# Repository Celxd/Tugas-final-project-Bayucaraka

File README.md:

# Data Kelompok

| Nama | NRP | Prodi | Sub-divisi |
| --- | --- | --- | --- |
| Alif Gibran Muhammad Ervin | 5026251070 | Sistem Informasi | Programming |
| Kadek Rahayu Pradnyani | 2040251079 | Teknik Elektro Otomasi | Electrical |
| Ahmad Syahreza Nouval Siregar | 5002251169 | Matematika | Mekanik |

# Struktur Project
```
.
├── Electrical/
│   ├── Old/            (Demo Elektrikal)
│   ├── Revised/        (Revisi Elektrikal)
├── Mechanical/
│   ├── ...
├── Programming/
│   ├── revised_ros_ws/ (Revisi Programming)
│   └── OLD_final.py    (Demo Programming)
├── .gitignore
└── README.md
```

# Electrical
Beberapa peningkatan atau perbaikan yang dilakukan:  
- Ground plane ditempatkan di layer atas, sehingga distribusi ground lebih rapi dan stabil.
- Jalur sinyal dan jalur lainnya berada di layer bawah, untuk mempermudah routing dan meningkatkan connectivity antar komponen.
- Desain ini dibuat dengan mempertimbangkan kemudahan proses produksi di Toko Panut, sehingga layout lebih clean dan tidak terlalu kompleks untuk menyolder saat sudah dicetak.
- Clearance antar jalur diperlebar, sehingga proses penyolderan menjadi lebih mudah dan mengurangi risiko short circuit.

Secara desain dan layout, PCB sudah siap untuk tahap produksi dan assembly.

Namun, untuk saat ini pengujian penggerakan motor belum dapat dilakukan karena tidak dapat meminjam motor untuk dicoba.

# Programming
Logika awal programming:
- Cam detect tag0(payload)
- Send posisi tag0 ke mcu sampai tag0 dekat 0,0
- Send command "PAYLOAD" ke mcu agar mcu menggerakkan motor untuk mengambil payload
- Mcu mengirimkan command track drop lalu cam mendeteksi tag1
- Cam mengirimkan posisi tag1 ke mcu sampai tag1 dekat 0,0
- Mcu mengirimkan command "DROP" ke mcu agar mcu menggerakkan motor untuk menjatuhkan payload

Revisi (``Programming\revised_ros_ws``):
- Menggantikan koneksi langsung dengan serial menjadi koneksi melalui topic

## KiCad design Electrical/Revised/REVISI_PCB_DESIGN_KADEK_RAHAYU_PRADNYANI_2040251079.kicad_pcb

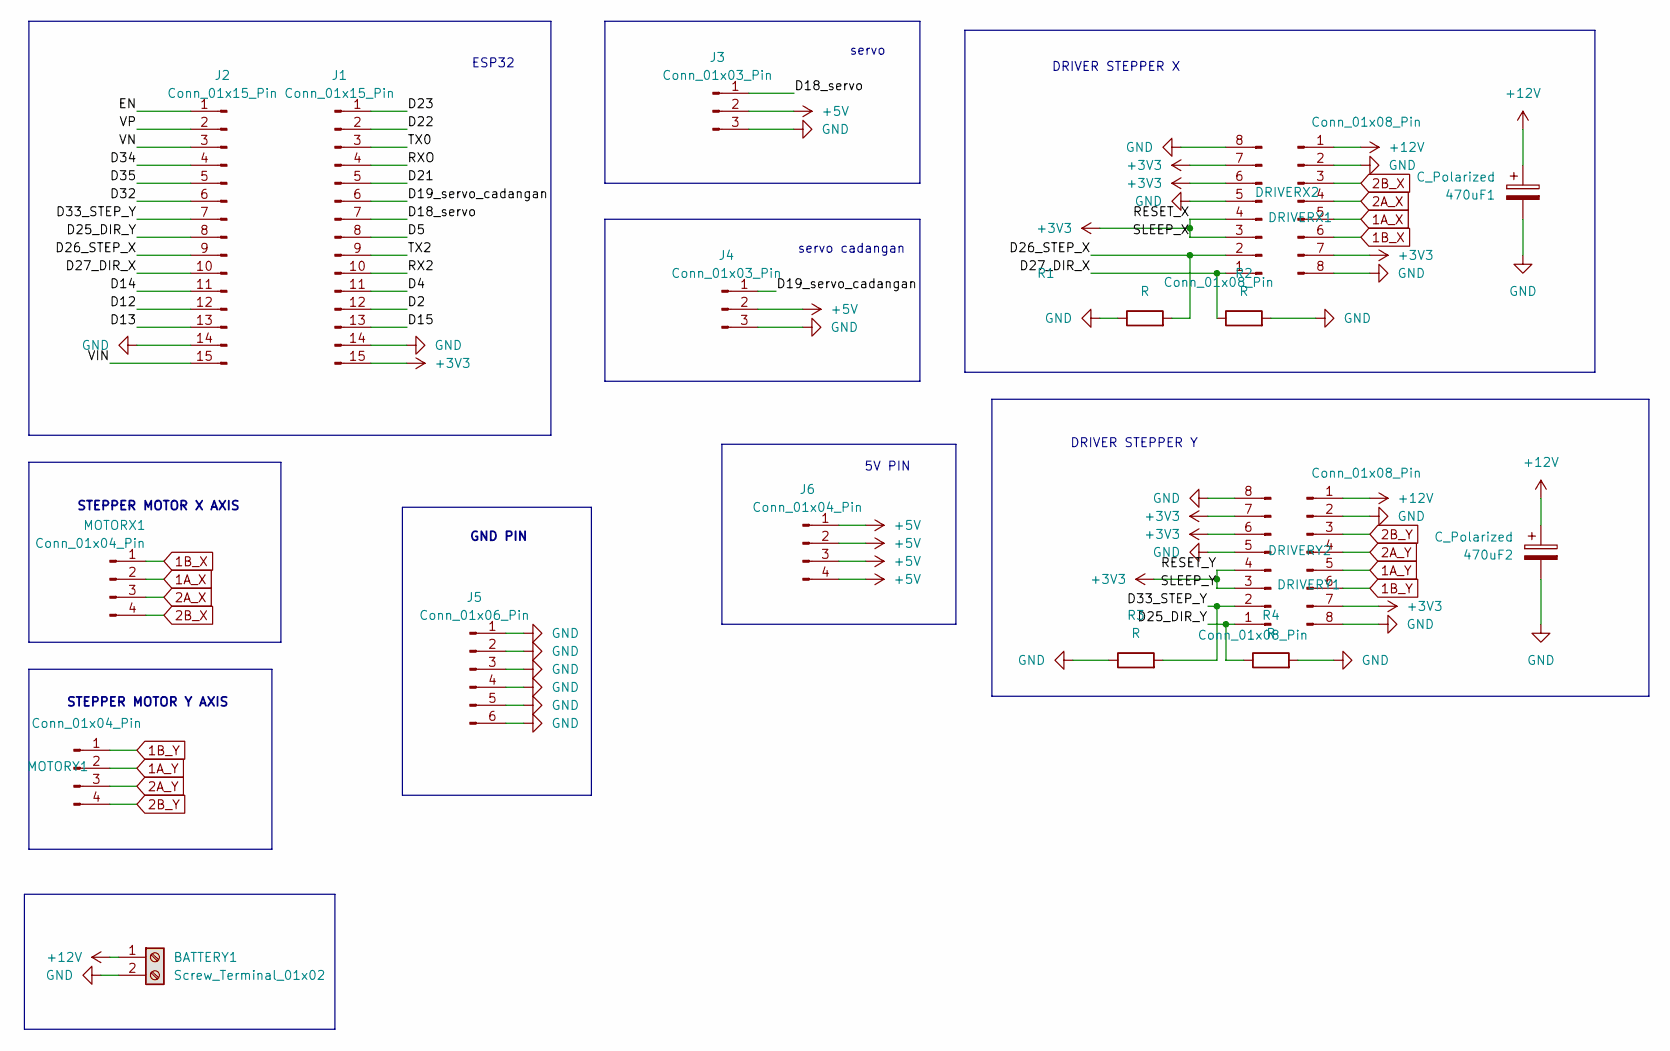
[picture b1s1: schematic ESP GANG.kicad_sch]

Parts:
470uF1, 470uF2: C_Polarized; CP_Radial_D8.0mm_P3.50mm
BATTERY1: Screw_Terminal_01x02; TerminalBlock_Phoenix_PT-1,5-2-3.5-H_1x02_P3.50mm_Horizontal
DRIVERX1, DRIVERX2: Conn_01x08_Pin; PinSocket_1x08_P2.54mm_Vertical
DRIVERY1, DRIVERY2: Conn_01x08_Pin; PinSocket_1x08_P2.54mm_Vertical
J1, J2: Conn_01x15_Pin; PinHeader_1x15_P2.54mm_Vertical
J3, J4: Conn_01x03_Pin; PinHeader_1x03_P2.54mm_Vertical
J5: Conn_01x06_Pin; PinSocket_1x06_P2.54mm_Vertical
J6: Conn_01x04_Pin; PinSocket_1x04_P2.54mm_Vertical
MOTORX1: Conn_01x04_Pin; PinSocket_1x04_P2.54mm_Vertical
MOTORY1: Conn_01x04_Pin; PinSocket_1x04_P2.54mm_Vertical
R1, R2, R3, R4: R; R_Axial_DIN0207_L6.3mm_D2.5mm_P7.62mm_Horizontal

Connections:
1A_X: DRIVERX2.5, MOTORX1.2
1A_Y: DRIVERY2.5, MOTORY1.2
1B_X: DRIVERX2.6, MOTORX1.1
1B_Y: DRIVERY2.6, MOTORY1.1
2A_X: DRIVERX2.4, MOTORX1.3
2A_Y: DRIVERY2.4, MOTORY1.3
2B_X: DRIVERX2.3, MOTORX1.4
2B_Y: DRIVERY2.3, MOTORY1.4
+5V: J3.2, J4.2, J6.1, J6.2, J6.3, J6.4
+12V: 470uF1.1, 470uF2.1, BATTERY1.1, DRIVERX2.1, DRIVERY2.1
/D2: J1.12
/D4: J1.11
/D5: J1.8
/D12: J2.12
/D13: J2.13
/D14: J2.11
/D15: J1.13
/D18_servo: J1.7, J3.1
/D19_servo_cadangan: J1.6, J4.1
/D21: J1.5
/D22: J1.2
/D23: J1.1
/D25_DIR_Y: DRIVERY1.1, J2.8, R4.1
/D26_STEP_X: DRIVERX1.2, J2.9, R1.2
/D27_DIR_X: DRIVERX1.1, J2.10, R2.1
/D32: J2.6
/D33_STEP_Y: DRIVERY1.2, J2.7, R3.2
/D34: J2.4
/D35: J2.5
/EN: J2.1
/RX2: J1.10
/RXO: J1.4
/TX0: J1.3
/TX2: J1.9
/VIN: J2.15
/VN: J2.3
/VP: J2.2

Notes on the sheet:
DRIVER STEPPER Y
STEPPER MOTOR X AXIS
servo cadangan
STEPPER MOTOR Y AXIS
DRIVER STEPPER X
servo
ESP32
GND PIN
5V PIN

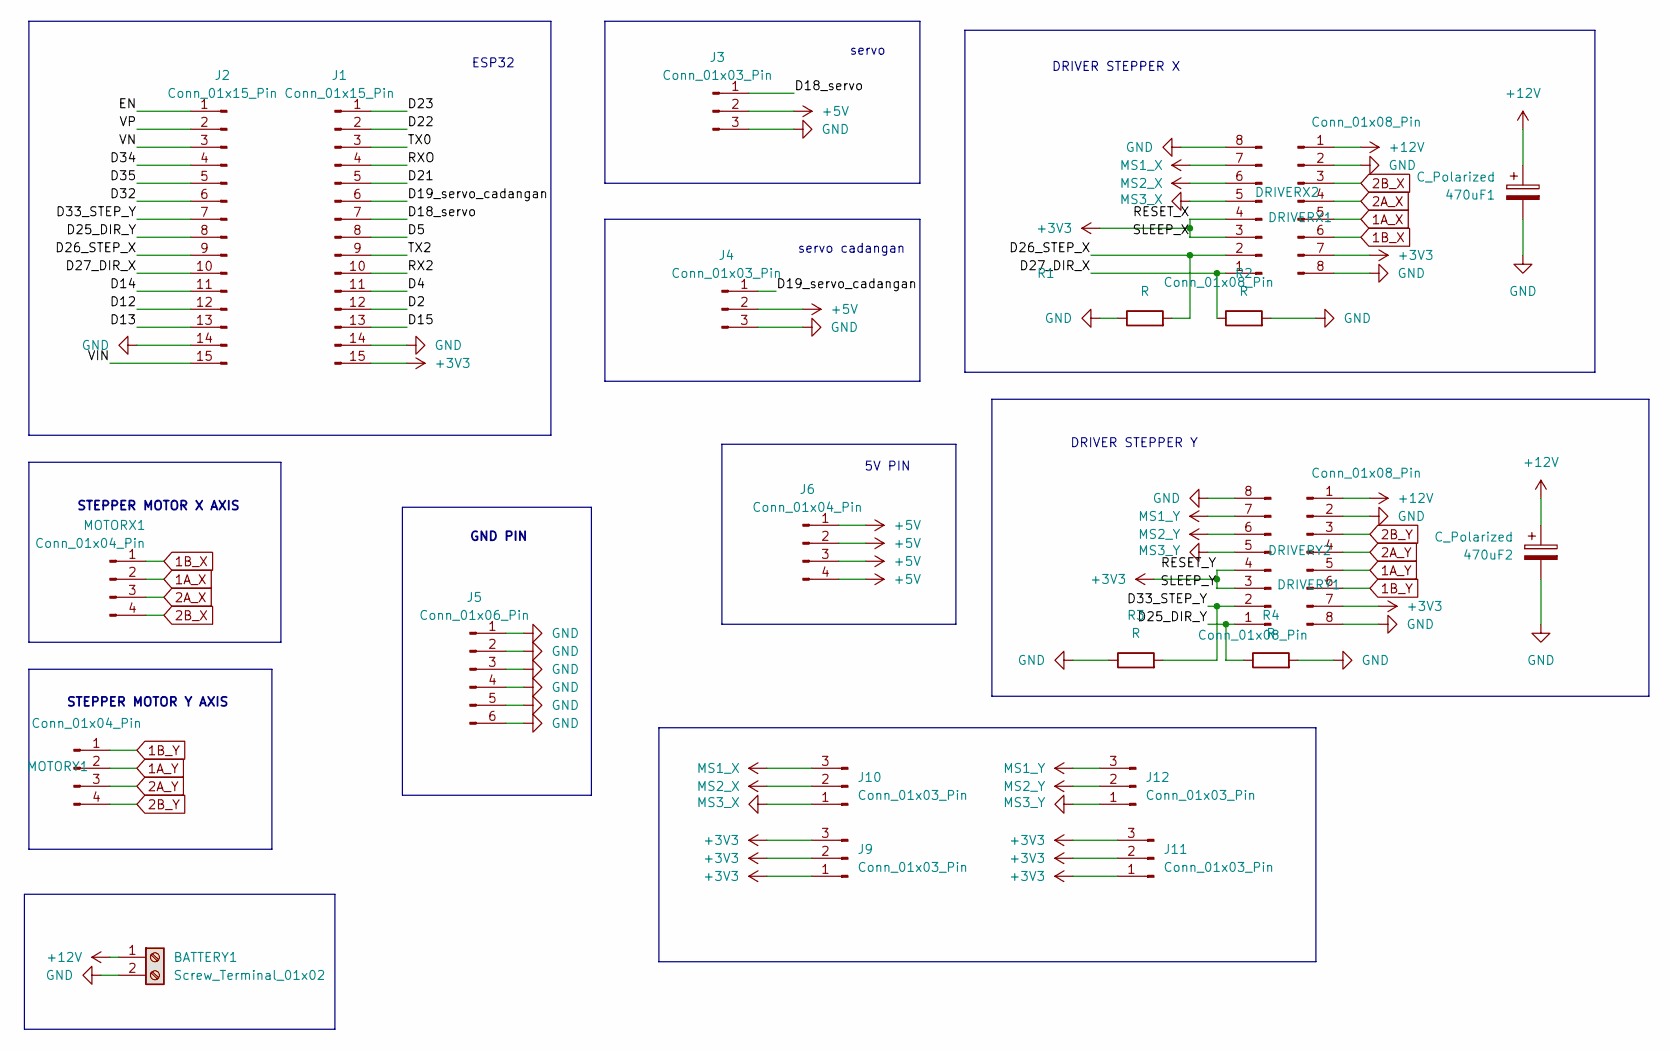
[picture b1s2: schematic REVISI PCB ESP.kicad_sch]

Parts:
470uF1, 470uF2: C_Polarized; CP_Radial_D8.0mm_P3.50mm
BATTERY1: Screw_Terminal_01x02; TerminalBlock_Phoenix_PT-1,5-2-3.5-H_1x02_P3.50mm_Horizontal
DRIVERX1, DRIVERX2: Conn_01x08_Pin; PinSocket_1x08_P2.54mm_Vertical
DRIVERY1, DRIVERY2: Conn_01x08_Pin; PinSocket_1x08_P2.54mm_Vertical
J1, J2: Conn_01x15_Pin; PinSocket_1x15_P2.54mm_Vertical
J3, J4: Conn_01x03_Pin; PinHeader_1x03_P2.54mm_Vertical
J5: Conn_01x06_Pin; PinSocket_1x06_P2.54mm_Vertical
J6: Conn_01x04_Pin; PinSocket_1x04_P2.54mm_Vertical
J9, J10, J11, J12: Conn_01x03_Pin; PinSocket_1x03_P2.54mm_Vertical
MOTORX1: Conn_01x04_Pin; PinHeader_1x04_P2.54mm_Vertical
MOTORY1: Conn_01x04_Pin; PinHeader_1x04_P2.54mm_Vertical
R1, R2, R3, R4: R; R_Axial_DIN0207_L6.3mm_D2.5mm_P7.62mm_Horizontal

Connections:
1A_X: DRIVERX2.5, MOTORX1.2
1A_Y: DRIVERY2.5, MOTORY1.2
1B_X: DRIVERX2.6, MOTORX1.1
1B_Y: DRIVERY2.6, MOTORY1.1
2A_X: DRIVERX2.4, MOTORX1.3
2A_Y: DRIVERY2.4, MOTORY1.3
2B_X: DRIVERX2.3, MOTORX1.4
2B_Y: DRIVERY2.3, MOTORY1.4
+5V: J3.2, J4.2, J6.1, J6.2, J6.3, J6.4
+12V: 470uF1.1, 470uF2.1, BATTERY1.1, DRIVERX2.1, DRIVERY2.1
/D2: J1.12
/D4: J1.11
/D5: J1.8
/D12: J2.12
/D13: J2.13
/D14: J2.11
/D15: J1.13
/D18_servo: J1.7, J3.1
/D19_servo_cadangan: J1.6, J4.1
/D21: J1.5
/D22: J1.2
/D23: J1.1
/D25_DIR_Y: DRIVERY1.1, J2.8, R4.1
/D26_STEP_X: DRIVERX1.2, J2.9, R1.2
/D27_DIR_X: DRIVERX1.1, J2.10, R2.1
/D32: J2.6
/D33_STEP_Y: DRIVERY1.2, J2.7, R3.2
/D34: J2.4
/D35: J2.5
/EN: J2.1
/RX2: J1.10
/RXO: J1.4
/TX0: J1.3
/TX2: J1.9
/VIN: J2.15
/VN: J2.3
/VP: J2.2

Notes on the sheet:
DRIVER STEPPER Y
STEPPER MOTOR X AXIS
5V PIN
DRIVER STEPPER X
ESP32
servo cadangan
STEPPER MOTOR Y AXIS
GND PIN
servo

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
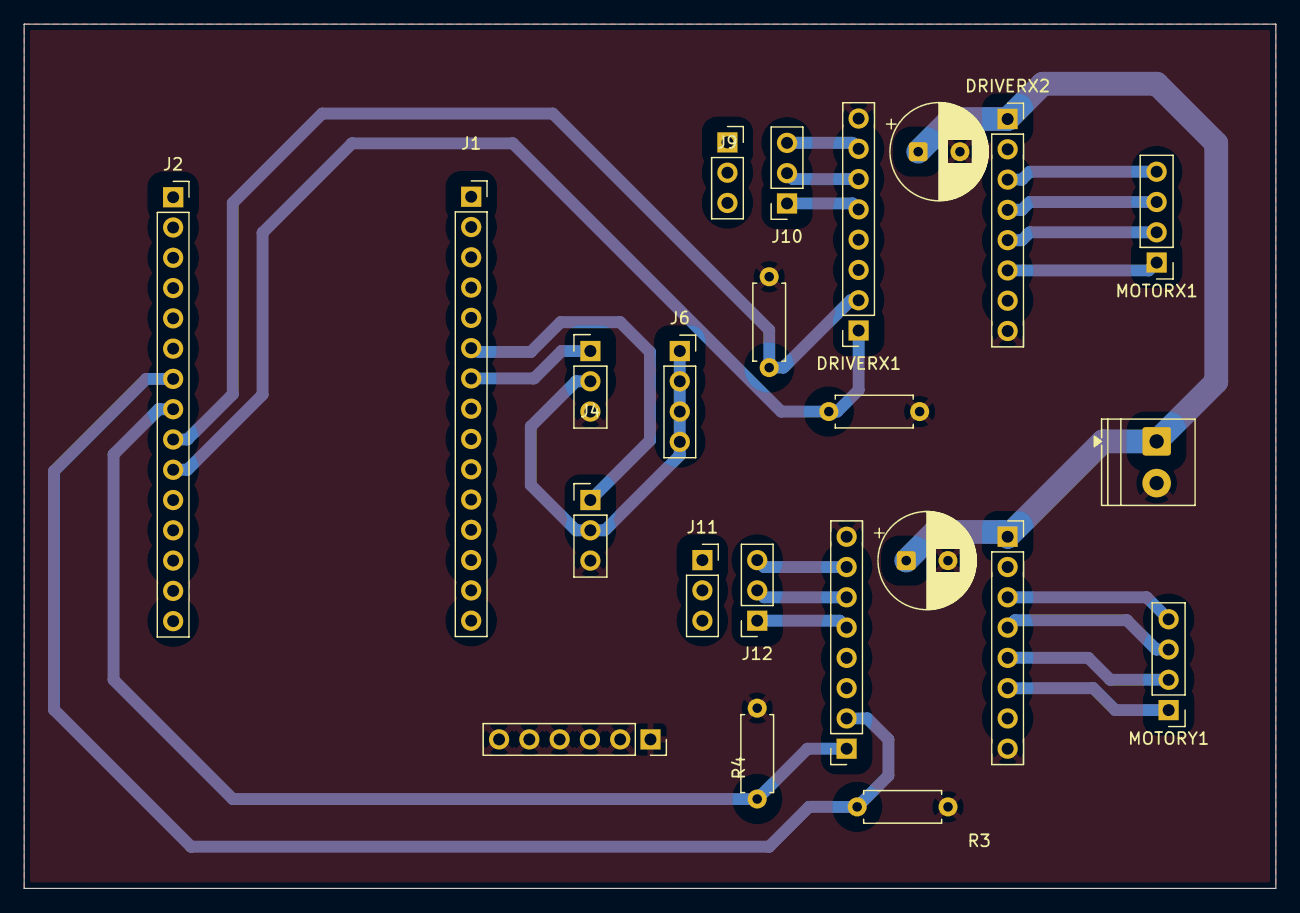
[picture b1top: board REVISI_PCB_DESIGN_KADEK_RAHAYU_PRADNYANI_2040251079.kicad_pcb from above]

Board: 2 copper layers, 105.0 x 72.5 mm, 23 parts (0 on the bottom side), 24 nets.

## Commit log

2026-03-02 Add files via upload
    Final untuk demo
2026-03-02 Video uji coba
2026-03-02 [Gib] style(folder): added seperate folders and gitignore
2026-03-02 [Gib] feat(OLD_final.py): added old demo script
2026-03-04 [Gib] feat(new script): Added ros integrated script, added comment to old
2026-03-04 [Gib] feat(electrical): added electrical files
2026-03-04 [Gib] feat(electrical): added revised files
2026-03-04 [Gib] docs(readme): added identification
2026-03-04 [Gib] feat(electrical): added old esp script
2026-03-04 [Gib] docs(readme): added project struct and explanations
2026-03-04 [Gib] style(electrical): added revised and old folders
2026-03-05 Add NRP for Ahmad Syahreza Nouval Siregar
